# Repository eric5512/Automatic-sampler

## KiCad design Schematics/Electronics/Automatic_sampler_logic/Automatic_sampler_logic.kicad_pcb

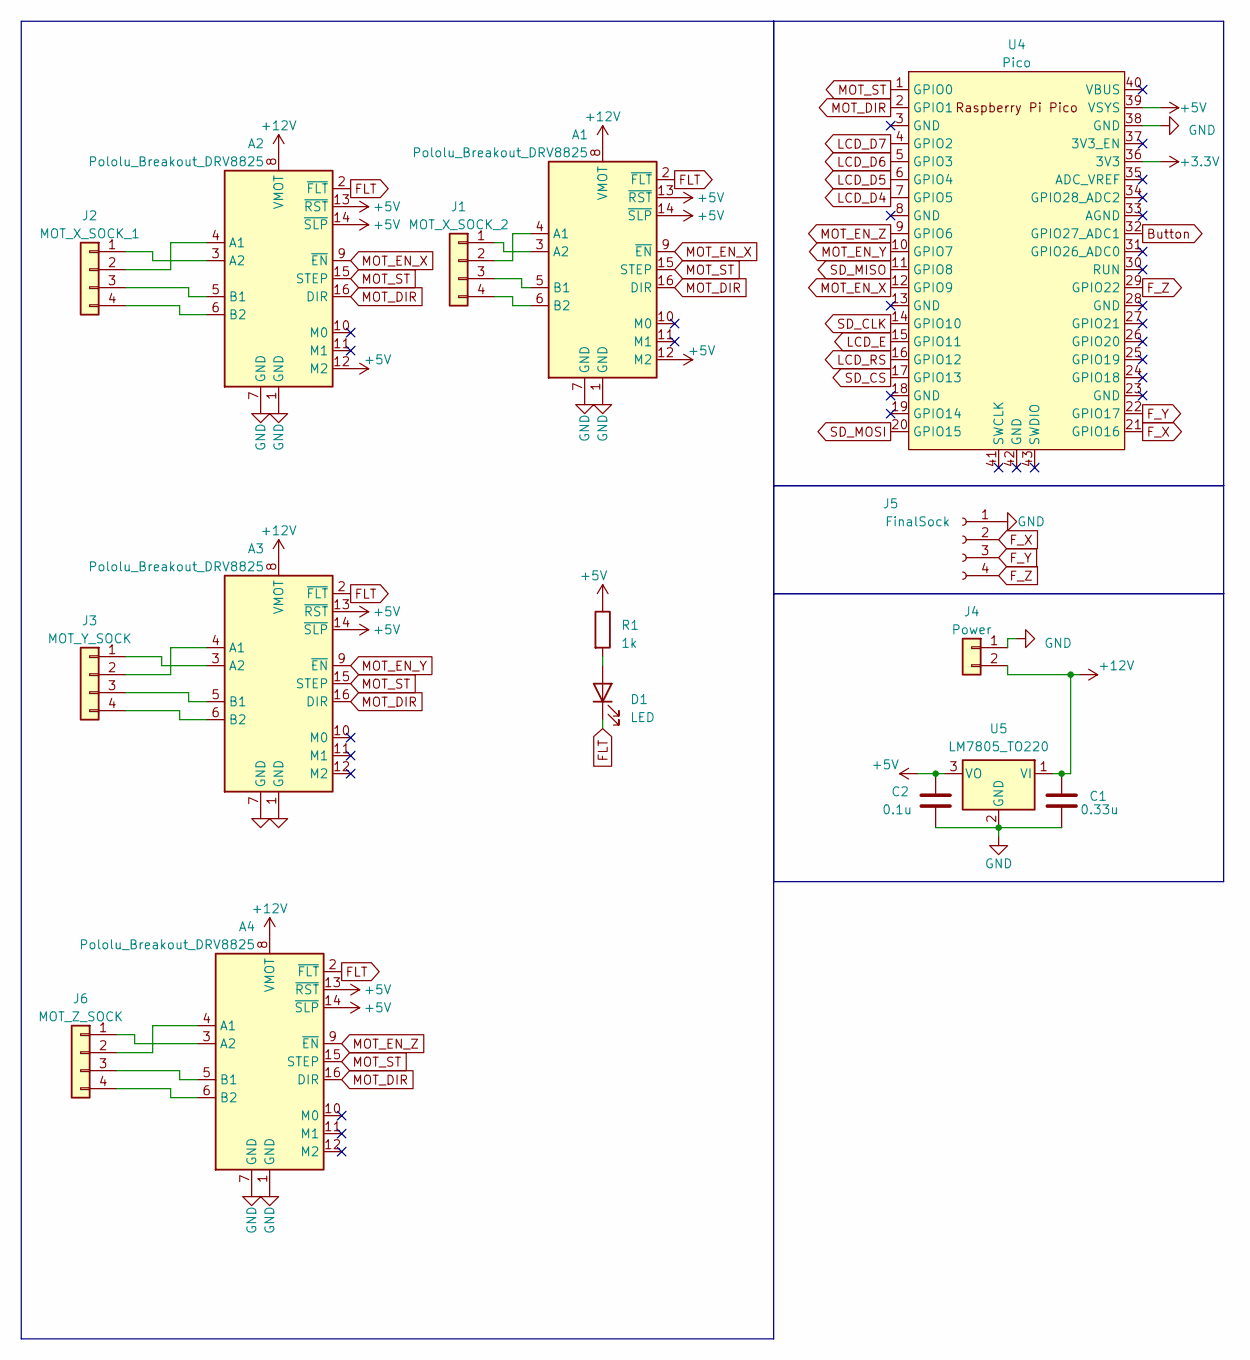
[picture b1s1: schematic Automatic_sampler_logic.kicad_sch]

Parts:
A1, A2, A3, A4: Pololu_Breakout_DRV8825; Pololu_Breakout-16_15.2x20.3mm
C1: 0.33u; C_Disc_D6.0mm_W2.5mm_P5.00mm
C2: 0.1u; C_Disc_D6.0mm_W2.5mm_P5.00mm
D1: LED; LED_D5.0mm
J1: MOT_X_SOCK_2; JST_PH_B4B-PH-K_1x04_P2.00mm_Vertical
J2: MOT_X_SOCK_1; JST_PH_B4B-PH-K_1x04_P2.00mm_Vertical
J3: MOT_Y_SOCK; JST_PH_B4B-PH-K_1x04_P2.00mm_Vertical
J4: Power; PinSocket_1x02_P2.54mm_Vertical
J5: FinalSock; PinSocket_1x04_P2.54mm_Vertical
J6: MOT_Z_SOCK; JST_PH_B4B-PH-K_1x04_P2.00mm_Vertical
R1: 1k; R_Axial_DIN0207_L6.3mm_D2.5mm_P7.62mm_Horizontal
U4: Pico; RPi_Pico_SMD_TH
U5: LM7805_TO220; TO-220-3_Vertical

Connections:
+3.3V: U4.36 (3V3)
+5V: A1.12 (M2), A1.13 (~RST), A1.14 (~SLP), A2.12 (M2), A2.13 (~RST), A2.14 (~SLP), A3.13 (~RST), A3.14 (~SLP), A4.13 (~RST), A4.14 (~SLP), C2.1, R1.1, U4.39 (VSYS), U5.3 (VO)
+12V: A1.8 (VMOT), A2.8 (VMOT), A3.8 (VMOT), A4.8 (VMOT), C1.1, J4.2, U5.1 (VI)
Button: U4.32 (GPIO27_ADC1)
FLT: A1.2 (~FLT), A2.2 (~FLT), A3.2 (~FLT), A4.2 (~FLT), D1.1 (K)
F_X: J5.2, U4.21 (GPIO16)
F_Y: J5.3, U4.22 (GPIO17)
F_Z: J5.4, U4.29 (GPIO22)
GND: A1.1 (GND), A1.7 (GND), A2.1 (GND), A2.7 (GND), A3.1 (GND), A3.7 (GND), A4.1 (GND), A4.7 (GND), C1.2, C2.2, J4.1, J5.1, U4.38 (GND), U5.2 (GND)
LCD_D4: U4.7 (GPIO5)
LCD_D5: U4.6 (GPIO4)
LCD_D6: U4.5 (GPIO3)
LCD_D7: U4.4 (GPIO2)
LCD_E: U4.15 (GPIO11)
LCD_RS: U4.16 (GPIO12)
MOT_DIR: A1.16 (DIR), A2.16 (DIR), A3.16 (DIR), A4.16 (DIR), U4.2 (GPIO1)
MOT_EN_X: A1.9 (~EN), A2.9 (~EN), U4.12 (GPIO9)
MOT_EN_Y: A3.9 (~EN), U4.10 (GPIO7)
MOT_EN_Z: A4.9 (~EN), U4.9 (GPIO6)
MOT_ST: A1.15 (STEP), A2.15 (STEP), A3.15 (STEP), A4.15 (STEP), U4.1 (GPIO0)
unnamed: A1.4 (A1), J1.2
unnamed: A1.3 (A2), J1.1
unnamed: A1.5 (B1), J1.3
unnamed: A1.6 (B2), J1.4
unnamed: A2.4 (A1), J2.2
unnamed: A2.3 (A2), J2.1
unnamed: A2.5 (B1), J2.3
unnamed: A2.6 (B2), J2.4
unnamed: A3.4 (A1), J3.2
unnamed: A3.3 (A2), J3.1
unnamed: A3.5 (B1), J3.3
unnamed: A3.6 (B2), J3.4
unnamed: A4.4 (A1), J6.2
unnamed: A4.3 (A2), J6.1
unnamed: A4.5 (B1), J6.3
unnamed: A4.6 (B2), J6.4
unnamed: D1.2 (A), R1.2
SD_CLK: U4.14 (GPIO10)
SD_CS: U4.17 (GPIO13)
SD_MISO: U4.11 (GPIO8)
SD_MOSI: U4.20 (GPIO15)

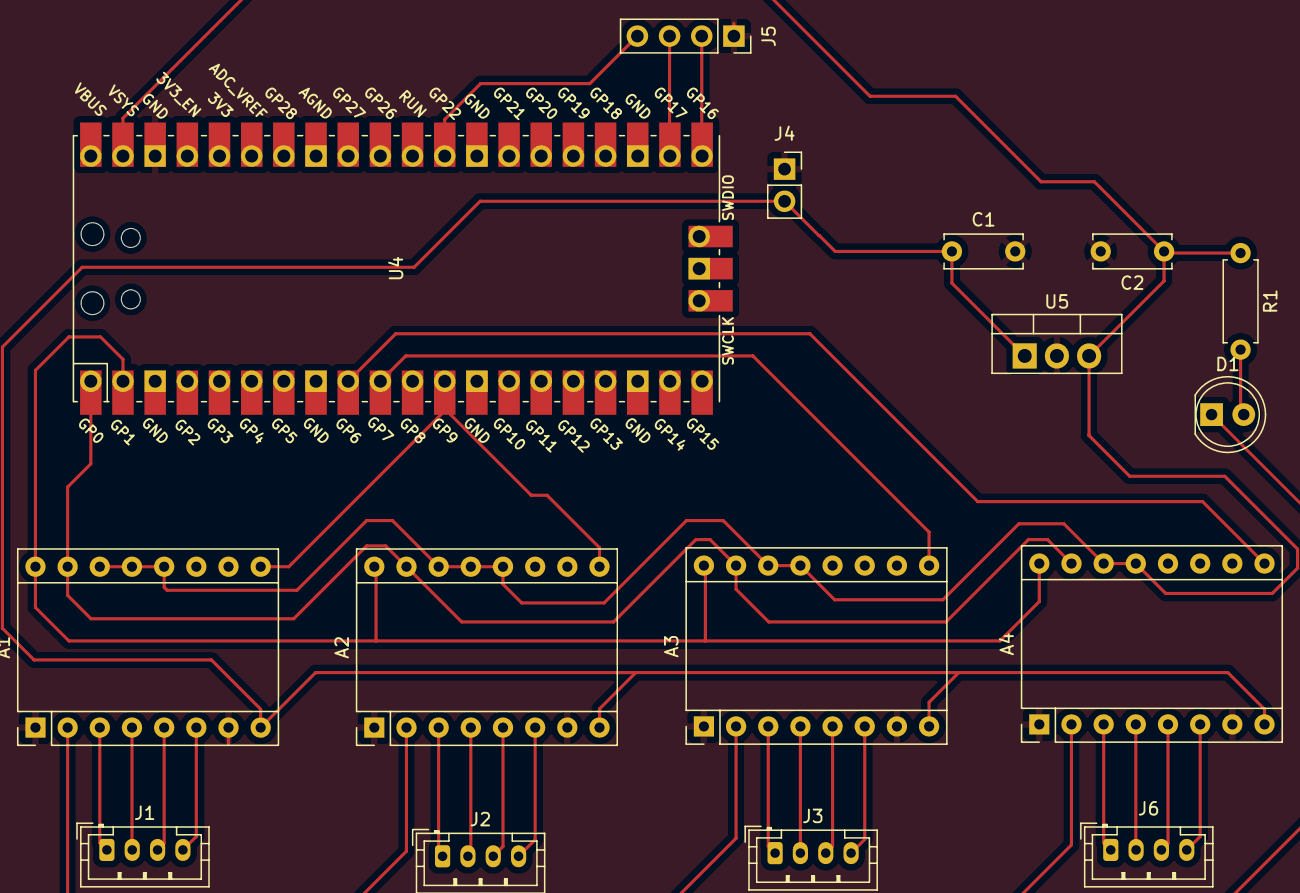
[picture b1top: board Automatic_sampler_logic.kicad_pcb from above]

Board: 2 copper layers, 16 parts (0 on the bottom side), 29 nets.

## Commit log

2023-09-08 Adding electronic schematics
2023-10-10 Added end to motor object
2023-10-10 Adding coord_t type
2023-10-12 Changes in MH and defining motor constants
2023-10-23 Added KiCad subprojects
2023-12-02 Changed schematics
2024-01-16 Gerber generated
2024-01-22 Added drill files
2024-04-25 Added independent delay to each axis
2024-04-26 Separating constants
    Separating constants of each motor
2024-04-30 Correcting errors
2024-04-30 Major circuit changes
    Removed from the circuit and the firmware the LCD and the SD card. They will be substituted by serial communication.
2024-05-01 Firmware update, ready to test
2024-05-01 Firmware minor issue fixing
2024-05-01 Major bugs fixed
2024-05-01 Moved UI to PyQt
2024-05-03 Added connect screen
2024-05-03 Added functionality to manual buttons
2024-05-03 Error fix
2024-05-11 Added separate thread to UI
    Added multithreading to wait the response from the machine
2024-05-11 Updating schematic
2024-05-11 Made PCB for AS
2024-06-08 Adding fabrication outputs to gitignore
2024-06-08 Creating sensor interface
2024-06-08 Working on sensor interface
2024-06-19 Working on 3D display
2024-06-23 Implementing automatic mode
    Implementing automatic mode + bugfixing
2024-06-27 Automatic movement implemented
2024-06-27 Created sensor proxy
    Created a proxy to handle the 32bit process and implemented reading almost compleatly
2024-09-04 Bug solving
